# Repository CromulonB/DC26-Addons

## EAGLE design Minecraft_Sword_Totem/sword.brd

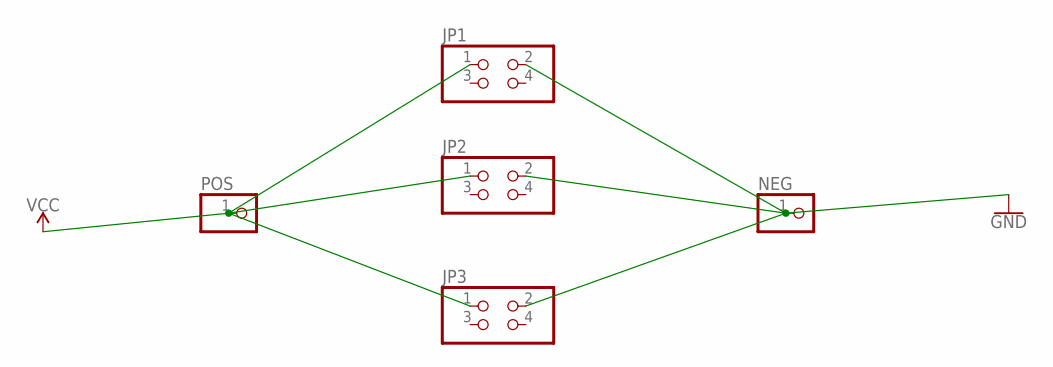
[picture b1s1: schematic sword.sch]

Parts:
JP1, JP2, JP3: PINHD-2X2; 2X02
NEG: PINHD-1X1; 1X01
POS: PINHD-1X1; 1X01

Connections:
GND: JP1.2, JP2.2, JP3.2, NEG.1
VCC: JP1.1, JP2.1, JP3.1, POS.1

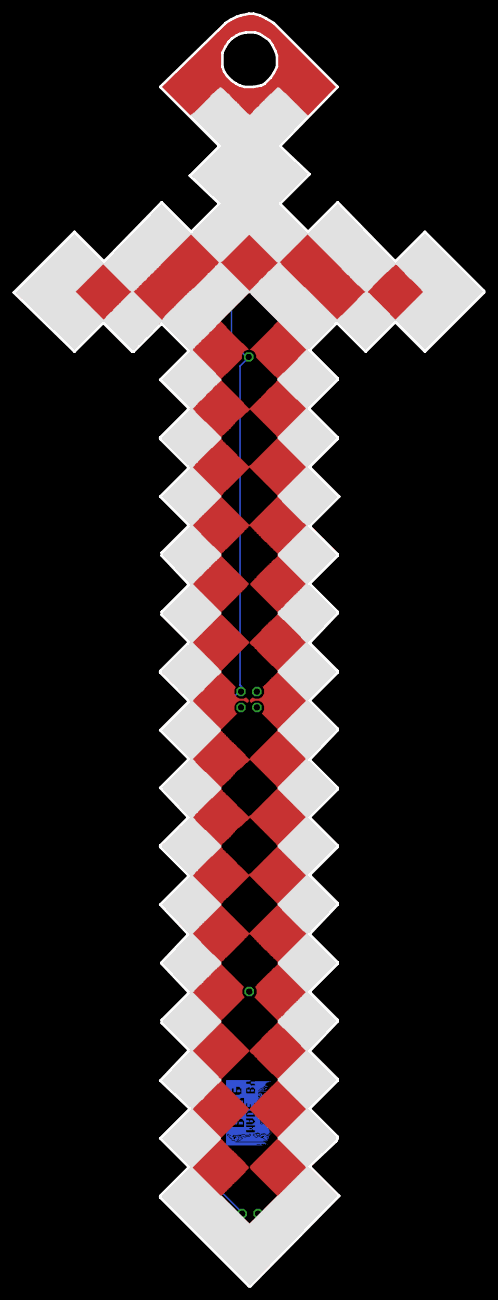
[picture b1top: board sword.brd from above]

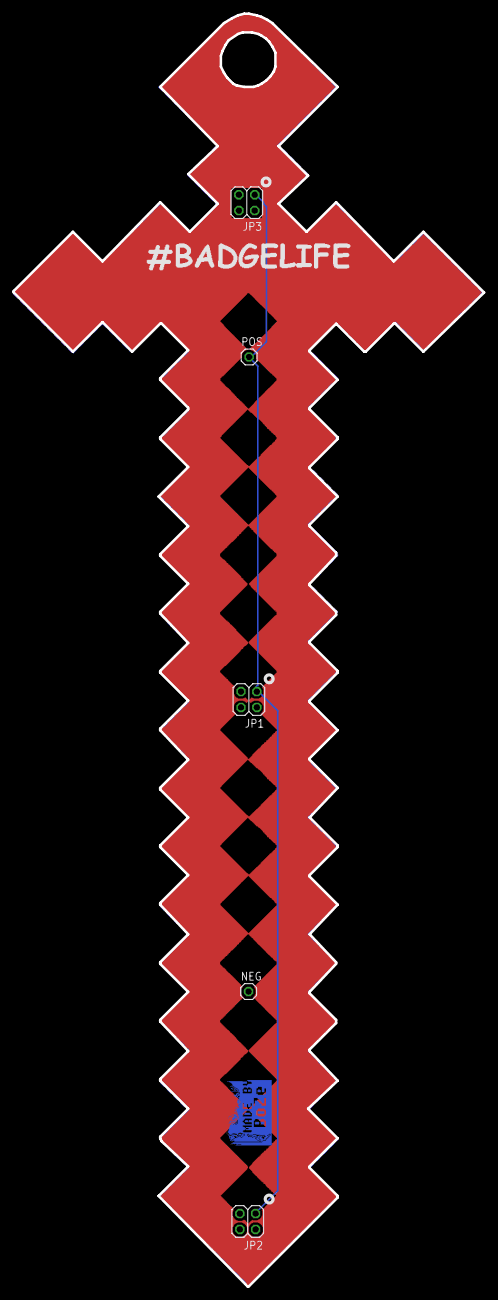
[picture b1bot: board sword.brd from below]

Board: 2 copper layers, 75.5 x 204.2 mm, 5 parts (5 on the bottom side), 2 nets.

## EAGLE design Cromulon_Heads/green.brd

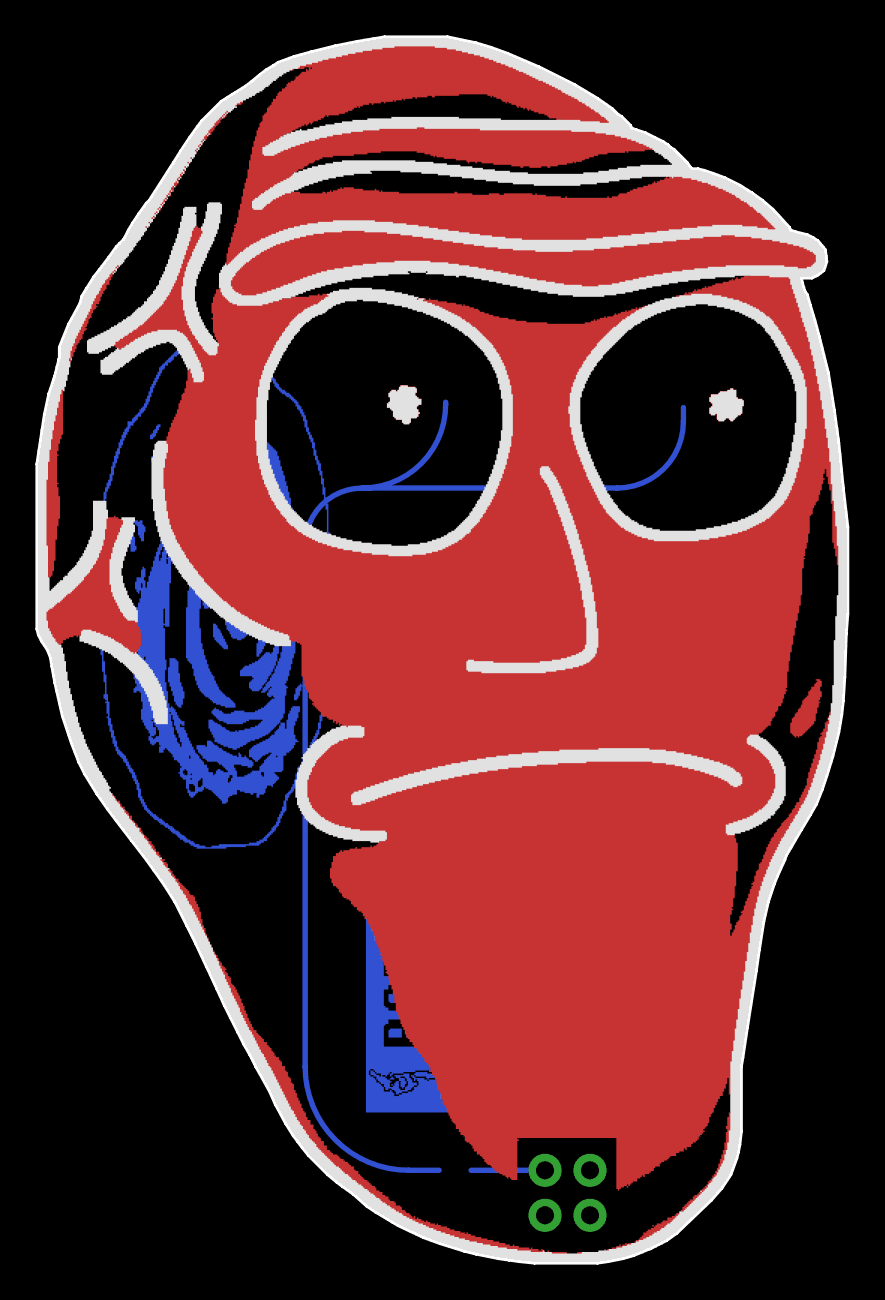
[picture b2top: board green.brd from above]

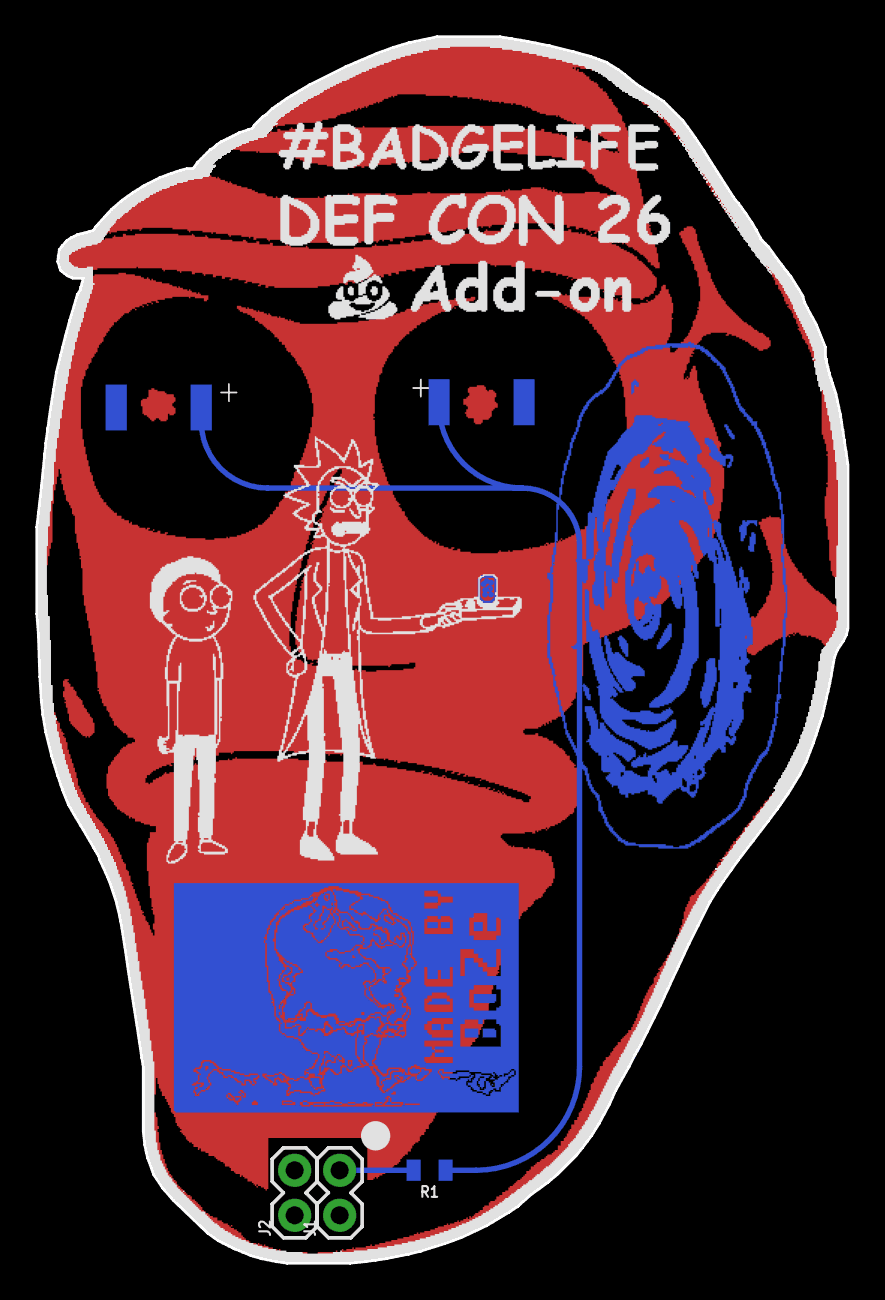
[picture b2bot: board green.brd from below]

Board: 2 copper layers, 45.8 x 69.3 mm, 5 parts (5 on the bottom side), 3 nets.

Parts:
J1, J2: 1X02
LED1, LED2: REVERSE_LED; REV_LED
R1: 0805

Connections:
GND: J1.1, LED1.P$2, LED2.P$2
unnamed: LED1.P$1, LED2.P$1, R1.1
VCC: J1.2, R1.2

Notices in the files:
parts and their libraries:
SparkFun-Connectors: Licensing: Creative Commons ShareAlike 4.0 International - https://creativecommons.org/licenses/by-sa/4.0
